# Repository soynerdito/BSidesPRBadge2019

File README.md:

# Never worked. Circuit has unknown issues.
Prototype made but never worked. Nor propertly tested or fixed.
Project left here for reference because maybe one day I would re try this design and make it work.

# Fail atempt for BSidesPR Badge
As part of BSidesPR we like to share a badge with participants. Ideally eveyone will have a badge to take home. Some times we might run out of badges. Still we strive for success.

## CPU
Badge uses one Atmega16U2 microcontroller. Minimal hardware is included in badge.

At the moment of publishing this repository it is unknown if this design will persist. Mostly due to it's cost and ensabling options.

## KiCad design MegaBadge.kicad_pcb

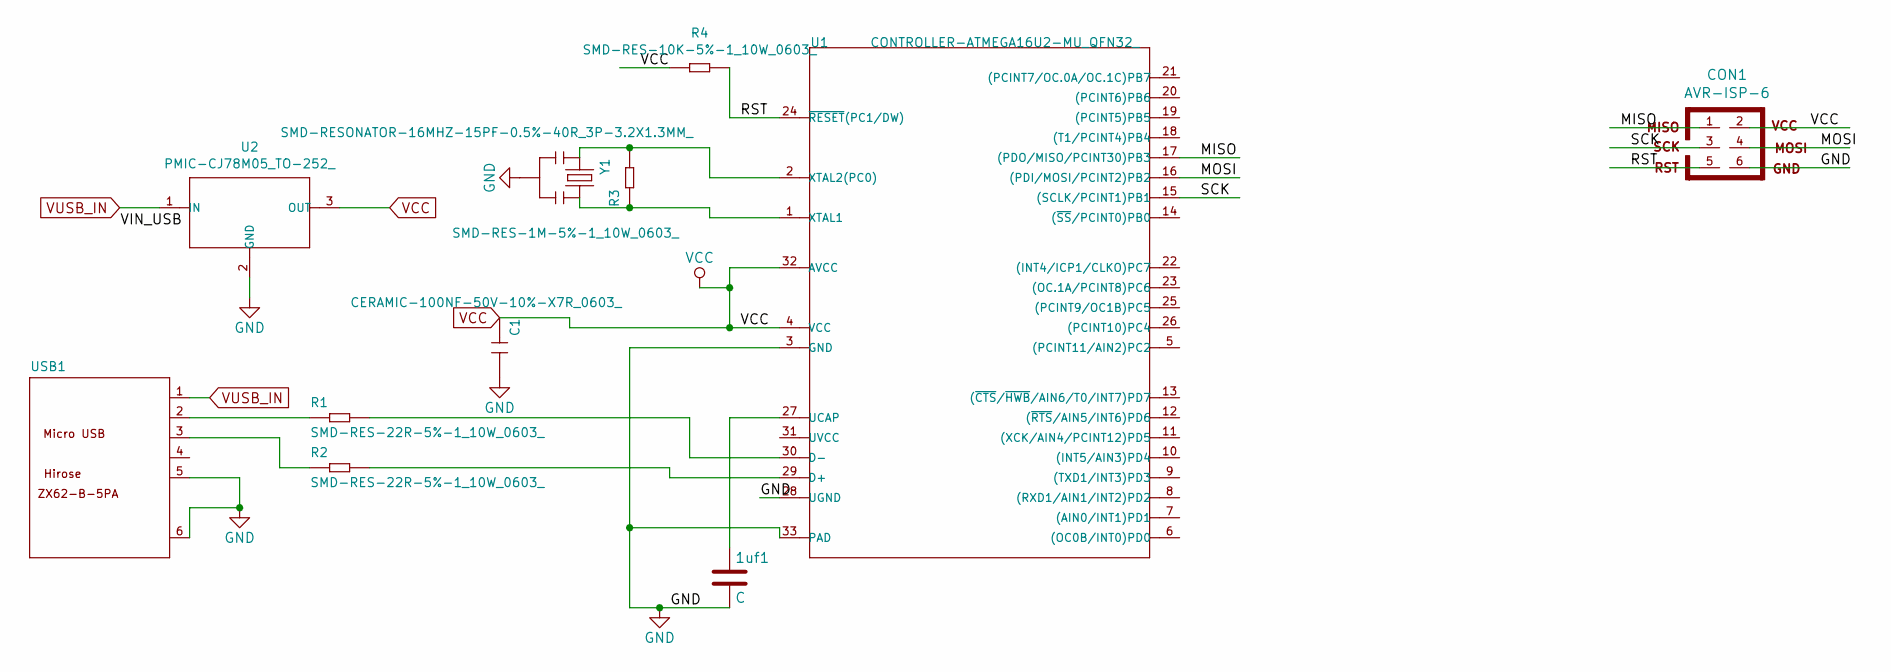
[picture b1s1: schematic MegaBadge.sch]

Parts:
1uf1: C; C0603; MPN CC0603KRX7R8BB105
C1: CERAMIC-100NF-50V-10%-X7R_0603_; C0603; MPN CC0603KRX7R9BB104
CON1: AVR-ISP-6; H2X3-2.54
R1, R2: SMD-RES-22R-5%-1_10W_0603_; R_0603; MPN RC0603JR-0722RL
R3: SMD-RES-1M-5%-1_10W_0603_; R_0603; MPN RC0603JR-071ML
R4: SMD-RES-10K-5%-1_10W_0603_; R0603; MPN RC0603JR-0710KL
U1: CONTROLLER-ATMEGA16U2-MU_QFN32_; QFN32G-0.5-5X5MM
U2: PMIC-CJ78M05_TO-252_; TO-252-2_Rectifier; MPN CJ78M05
USB1: MICRO-USB-SMD_ZX62-B-5PA_; MICRO-USB5+6P-SMD-0.65-AB; MPN ZX62-B-5PA
Y1: SMD-RESONATOR-16MHZ-15PF-0.5%-40R_3P-3.2X1.3MM_; X3-SMD-3.6X1.3X0.8MM; MPN CSTCE16M0V53-R0

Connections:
/MISO: CON1.1, U1.17 ((PDO/MISO/PCINT30)PB3)
/MOSI: CON1.4, U1.16 ((PDI/MOSI/PCINT2)PB2)
/RST: CON1.5, R4.2, U1.24 (~RESET~(PC1/DW))
/SCK: CON1.3, U1.15 ((SCLK/PCINT1)PB1)
GND: 1uf1.2, C1.2, CON1.6, U1.3 (GND), U1.28 (UGND), U1.33 (PAD), U2.2 (GND), USB1.5 (GND), USB1.6 (SHIELD), USB1.7 (SHIELD), USB1.8 (SHIELD), USB1.9 (SHIELD), Y1.2
unnamed: 1uf1.1, U1.27 (UCAP)
unnamed: R1.1, USB1.2 (D-)
unnamed: R1.2, U1.30 (D-)
unnamed: R2.1, USB1.3 (D+)
unnamed: R2.2, U1.29 (D+)
unnamed: R3.1, U1.1 (XTAL1), Y1.3
unnamed: R3.2, U1.2 (XTAL2(PC0)), Y1.1
VCC: C1.1, CON1.2, R4.1, U1.4 (VCC), U1.32 (AVCC), U2.3 (OUT)
VUSB_IN: U2.1 (IN), USB1.1 (VBUS)

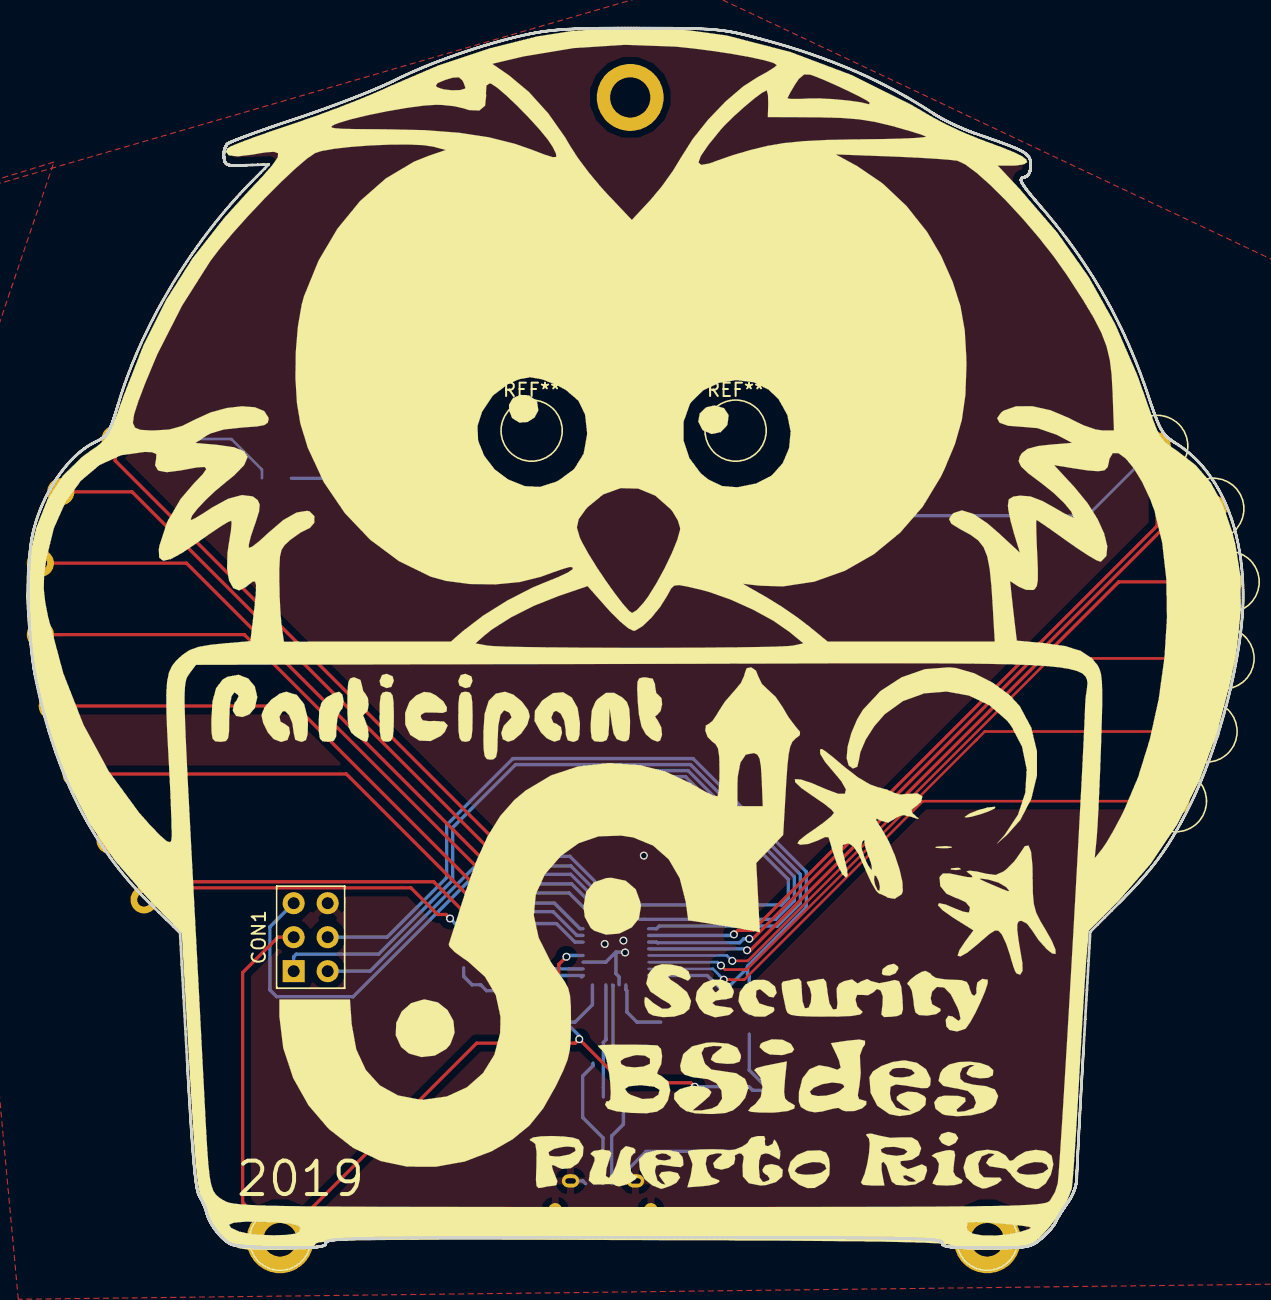
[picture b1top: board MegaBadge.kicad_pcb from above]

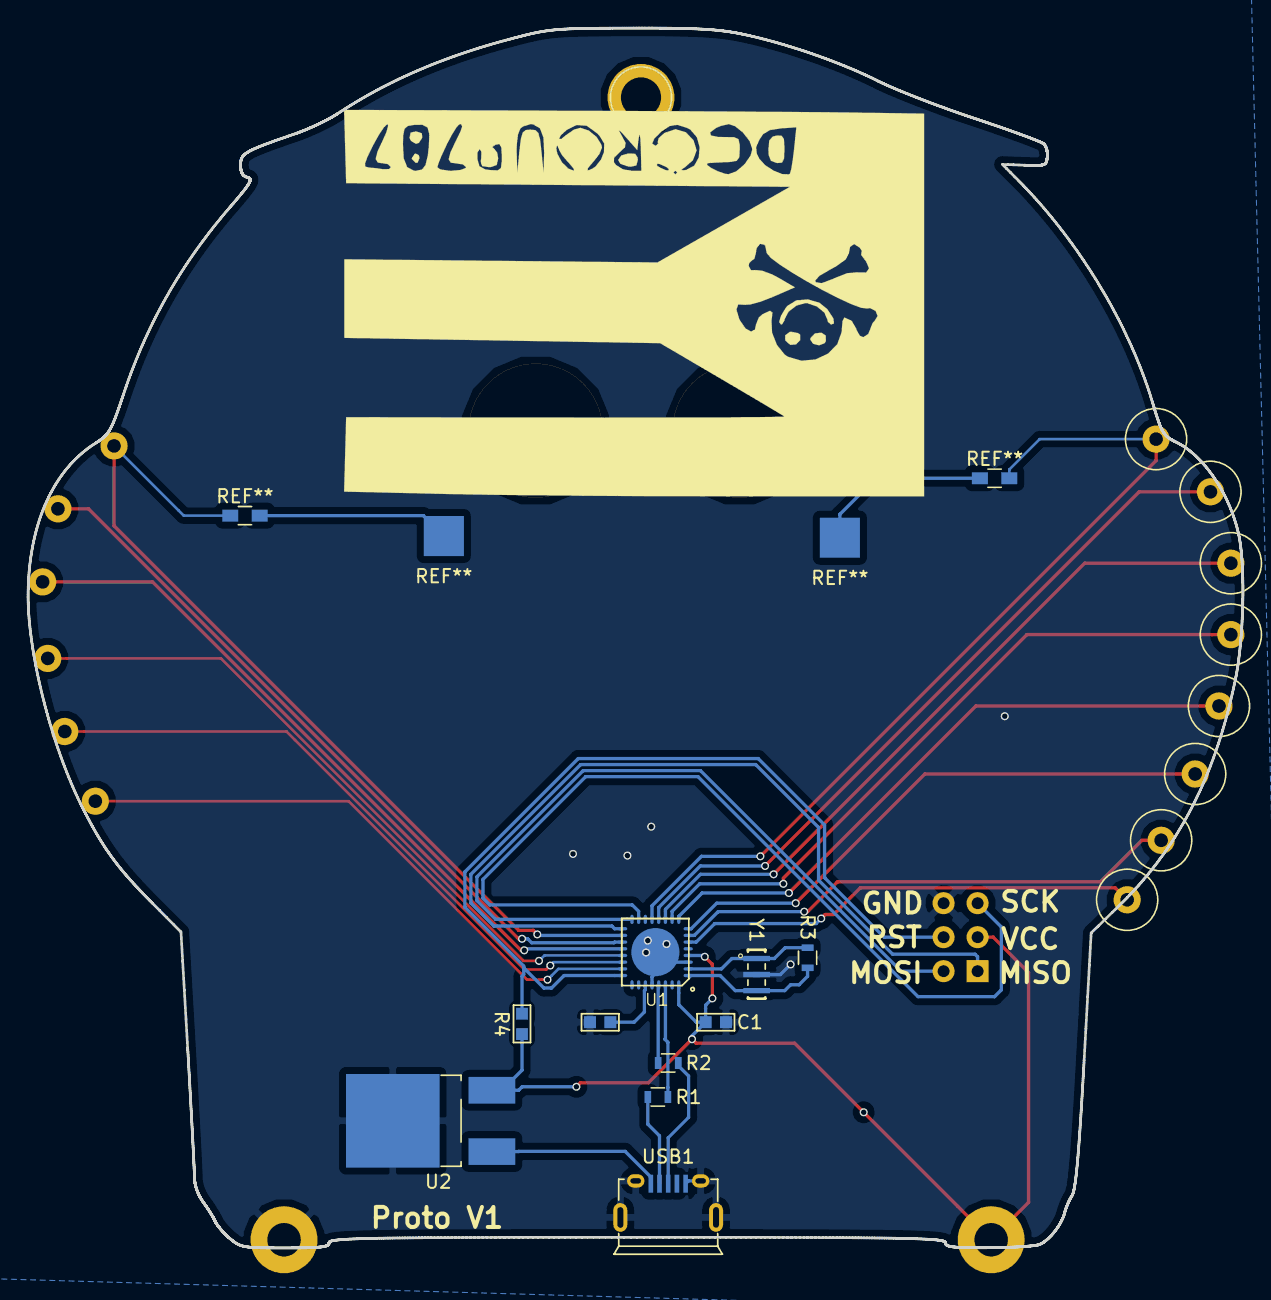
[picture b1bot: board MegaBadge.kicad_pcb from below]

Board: 2 copper layers, 90.8 x 91.1 mm, 11 parts (10 on the bottom side), 14 nets.

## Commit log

2019-02-26 Adding a readme
2019-02-26 Small changes, just adding some more comments
